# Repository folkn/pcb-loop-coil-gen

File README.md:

# pcb-loop-coil-gen

Generates a parametric, multi-segment, capacitor-loaded loop-antenna PCB in KiCad — entirely
through the KiCad IPC API ([kicad-python](https://gitlab.com/kicad/code/kicad-python) / `kipy`).
PCB editor only; no schematic is involved.

It draws a ring of copper trace segments around a large center hole, bridges the gaps between
segments with parallel capacitor sets, and feeds the loop through an edge-mount SMA connector.
The board outline is a donut with a rectangular tab at the feed that borders the SMA connector.

## Requirements

- KiCad 10.x with the IPC API server enabled (Preferences > Plugins > Enable KiCad API)
- Python 3.9+ and [kicad-python](https://gitlab.com/kicad/code/kicad-python) built against your
  KiCad install (see kicad-python's own `COMPILING.md`)
- The four footprints under `libraries/` are already included (`.kicad_mod` files) — two custom
  hand-made parts, a Knowles part, and KiCad's stock trimmer capacitor copied out locally

## Usage

1. Open `project/loop_coil.kicad_pcb` in KiCad's PCB editor (or any blank `.kicad_pcb`), with the
   IPC API server running.
2. Edit the parameters at the top of `generate_loop_coil.py` (hole diameter, trace width, number
   of segments, which capacitors to place, SMA orientation, etc).
3. Run it against the open board:
   ```sh
   python generate_loop_coil.py
   ```
   This edits the currently open board in place as a single undo step. It does not save the file
   itself — save from the GUI (Ctrl+S) or call `board.save()` yourself.

If re-running against a board that already has a previous generation on it, clear it first:
```python
from kipy import KiCad
board = KiCad().get_board()
board.remove_items(list(board.get_footprints()) + list(board.get_tracks()) + list(board.get_shapes()))
```

## Topology

The loop is a circle of N trace segments and N gaps, evenly distributed by angle. One gap is the
"feed" gap and contains the SMA connector; the other N-1 gaps each carry a user-chosen, identical
set of parallel capacitors bridging the two neighbouring segments.

At the feed gap: `coilLeft -- FEED_CAP_LEFT -- centerpad -- FEED_CAP_RIGHT -- coilRight`.
`coilRight` is tied directly (copper, no capacitor) to the SMA ground pads; `centerpad` drops
straight down to the SMA center pin. One segment therefore shares the GND net with the SMA ground
pads, while every other segment gets its own unique net (isolated by the capacitor gaps on both
sides).

See the module docstring in `generate_loop_coil.py` for the full picture, and `HANDOFF.md` for
implementation notes, environment quirks, and known simplifications (worth reading before making
nontrivial changes).

## Layout

```
generate_loop_coil.py   - the generator script; all user parameters are at the top
footprint_loader.py     - generic .kicad_mod parser + FootprintInstance builder (see HANDOFF.md
                          for why this exists: the IPC API has no "load footprint by name" call)
libraries/              - the .kicad_mod footprints this project uses
project/                - the KiCad project + board file
HANDOFF.md              - developer notes: environment setup, verification method, design
                          decisions and the reasoning behind them, known limitations
```

## Verifying changes

Don't trust low-resolution renders for fine detail — small parts placed a fraction of a
millimeter apart can look merged. Ground truth is the API: query `board.get_nets()` and each
footprint's `[(pad.number, pad.net.name) for pad in fp.definition.pads]` to check wiring, and pull
exact coordinates to check geometry (see `HANDOFF.md` for the matplotlib-based technique used
during development). For a quick visual check, `kicad-cli pcb export svg` works well.

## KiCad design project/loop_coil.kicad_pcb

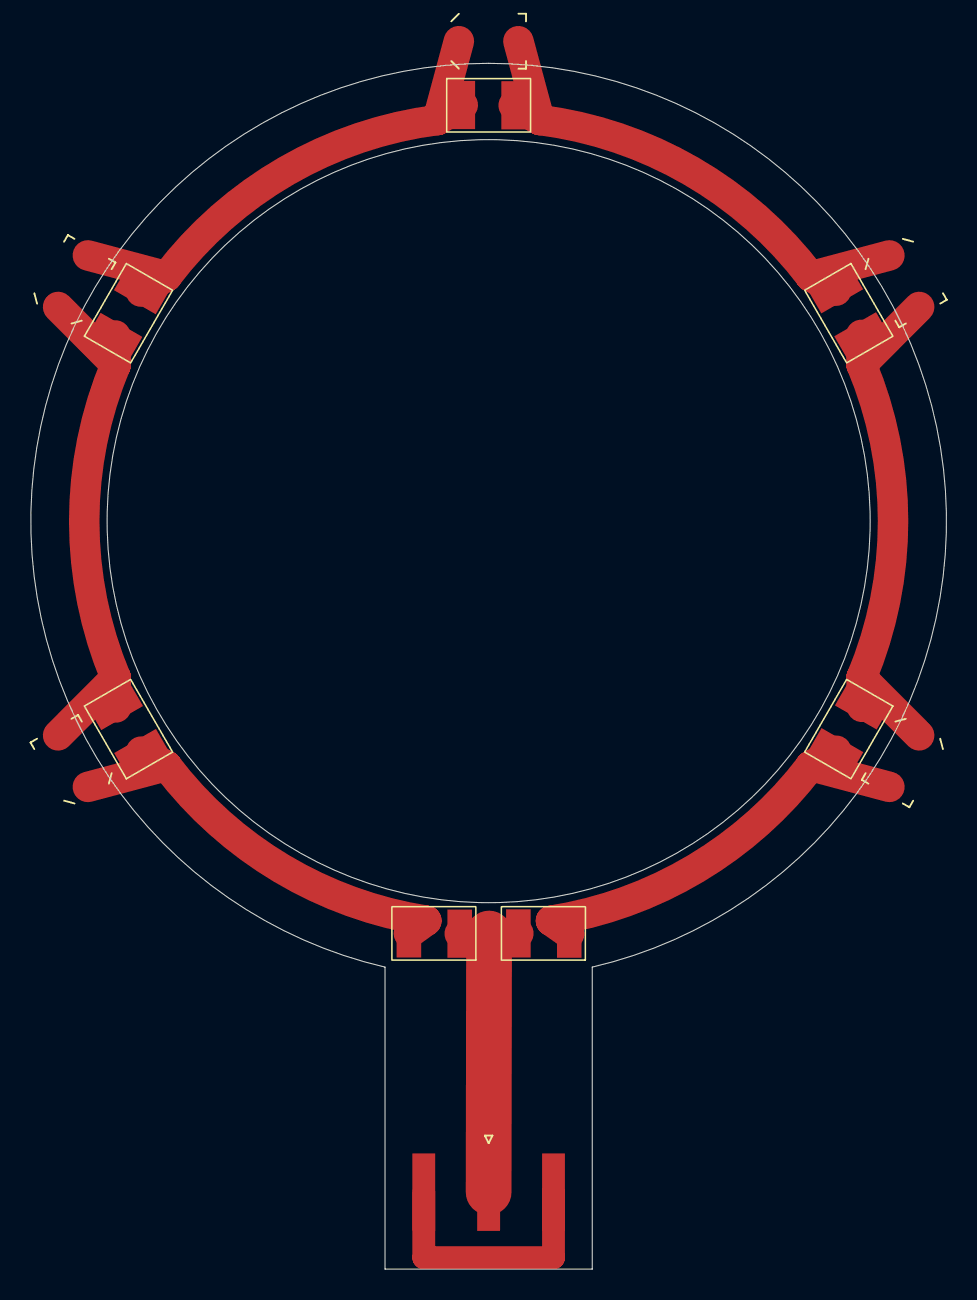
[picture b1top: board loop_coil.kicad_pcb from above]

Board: 2 copper layers, 60.0 x 79.0 mm, 13 parts (0 on the bottom side), 7 nets.

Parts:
C1, C3, C5, C7, C9, C11, C12: CAP_1111B-hand
C2, C4, C6, C8, C10: C_Trimmer_Voltronics_JZ
J1: SMA_Amphenol_132289_EdgeMount

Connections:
FEED: C11.1, C12.2, J1.1
GND: C9.2, C10.2, C12.1, J1.2
SEG_1: C1.1, C2.1, C11.2
SEG_2: C1.2, C2.2, C3.1, C4.1
SEG_3: C3.2, C4.2, C5.1, C6.1
SEG_4: C5.2, C6.2, C7.1, C8.1
SEG_5: C7.2, C8.2, C9.1, C10.1
